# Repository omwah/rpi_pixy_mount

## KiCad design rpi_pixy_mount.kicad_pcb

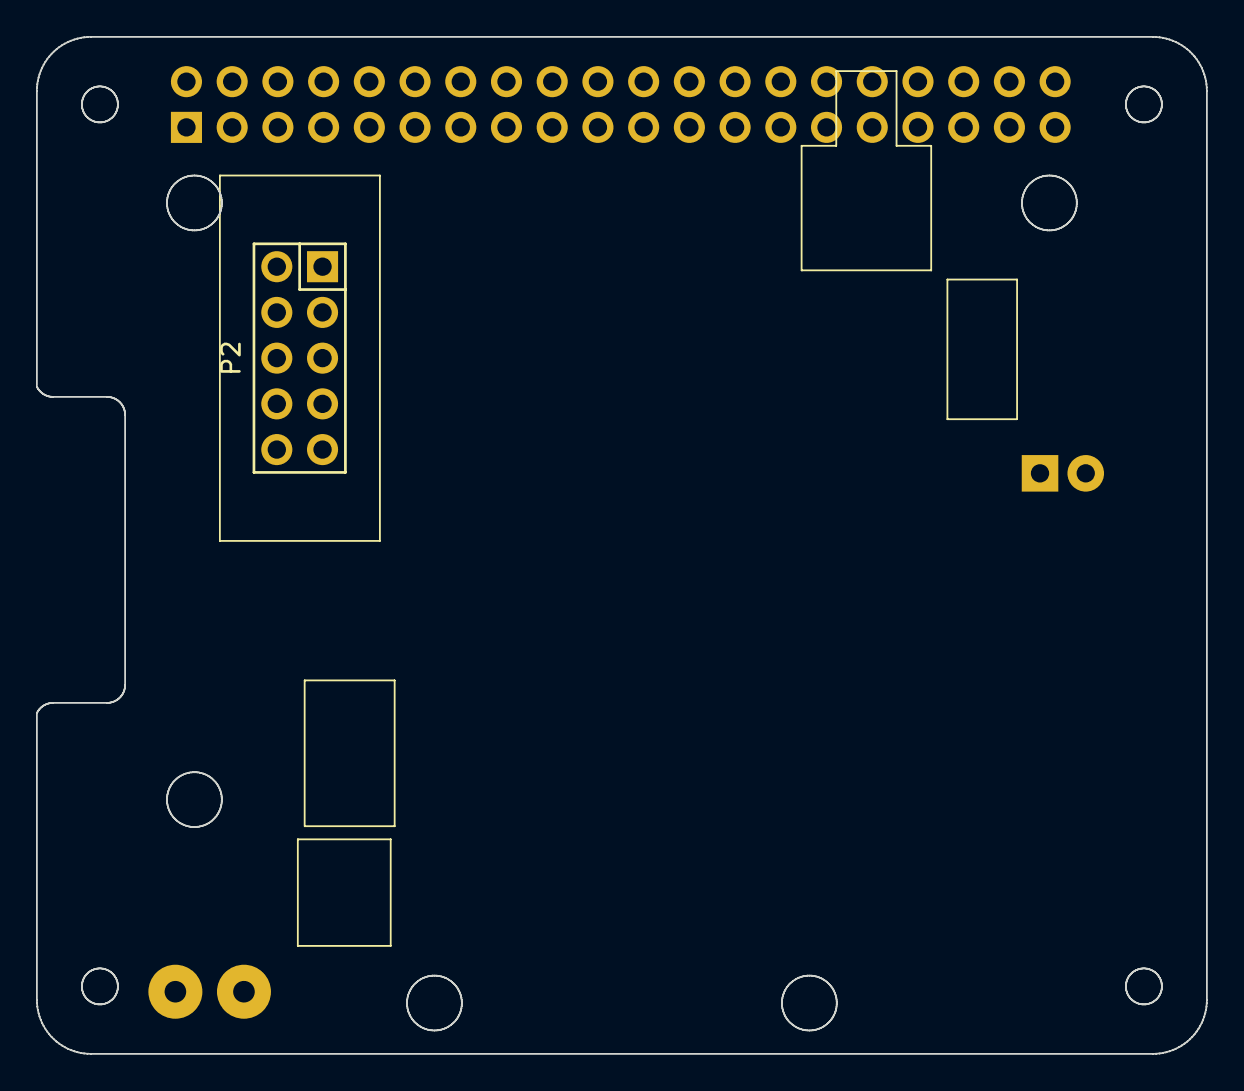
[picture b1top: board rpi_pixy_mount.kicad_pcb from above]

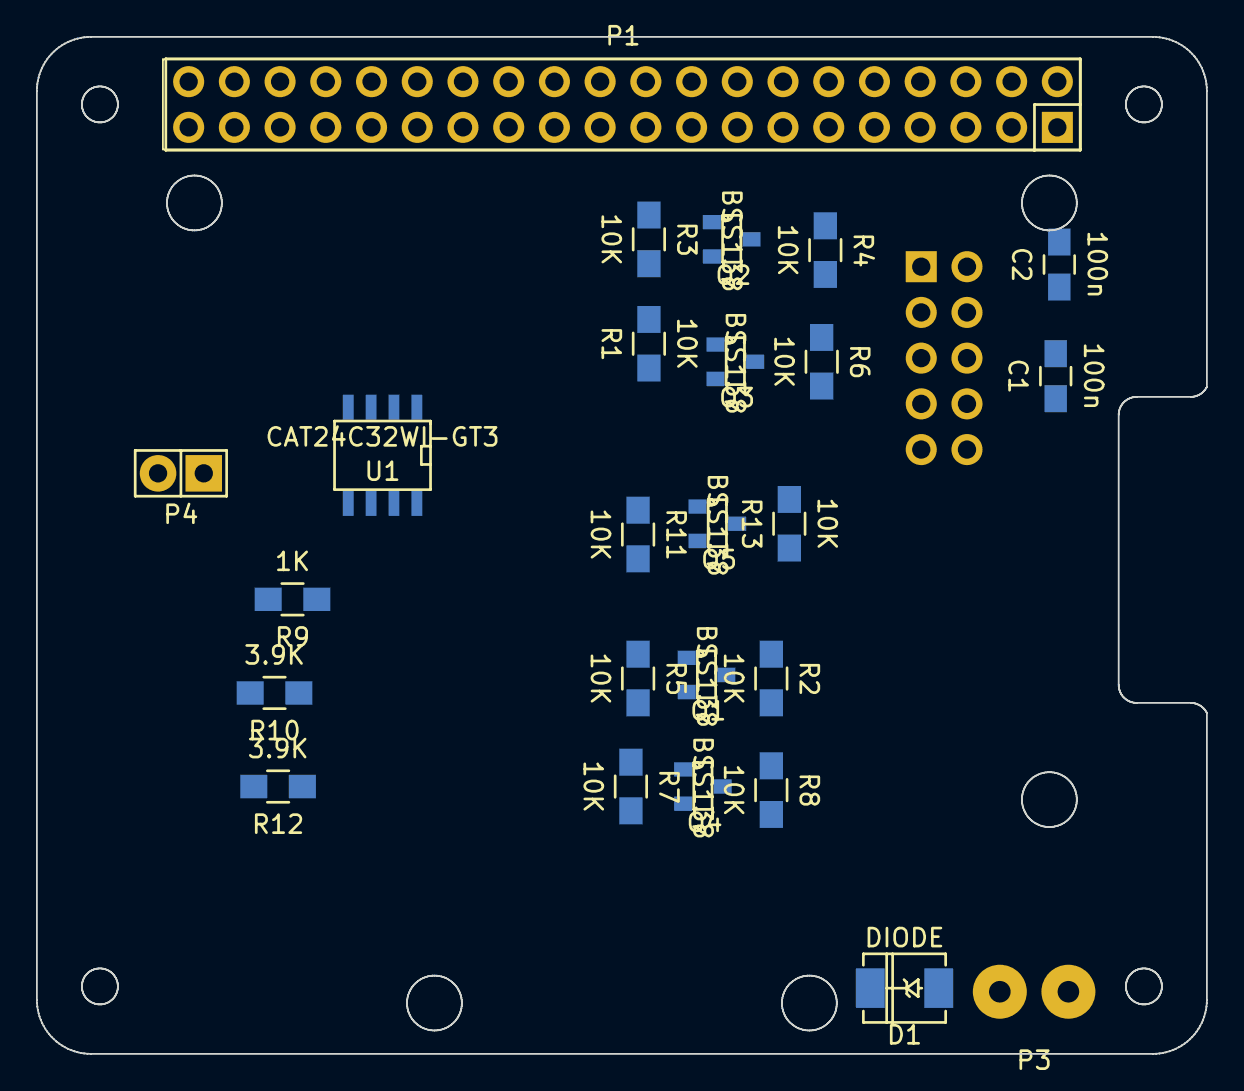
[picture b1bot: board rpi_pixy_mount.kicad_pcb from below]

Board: 2 copper layers, 65.0 x 56.5 mm, 26 parts (25 on the bottom side), 17 nets, no tracks yet.

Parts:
C1, C2: 100n; C_0805_HandSoldering
D1: DIODE; DO-214-AC_SMA
P1: RPi Connector; Socket_Strip_Straight_2x20
P2: Pixy Conn; Socket_Strip_Straight_2x05
P3: Power Input; SolderWirePad_2x_1-2mmDrill
P4: EEProm Write; Pin_Header_Straight_1x02
Q1, Q2, Q3, Q4, Q5: BSS138; SOT-23
R1, R2, R3, R4, R5, R6, R7, R8, R11, R13: 10K; R_0805_HandSoldering
R9: 1K; R_0805_HandSoldering
R10, R12: 3.9K; R_0805_HandSoldering
U1: CAT24C32WI-GT3; SOIC-8-W

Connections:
+3V3: C1.1, P1.1, Q1.1, Q2.1, Q3.1, Q4.1, Q5.1, R1.1, R3.1, R5.1, R7.1, R9.1, R10.1, R11.1, R12.1, U1.8
+5V: C2.1, D1.2, P1.2, P1.4, P2.2, R2.1, R4.1, R6.1, R8.1, R13.1
/ID_SC: P1.28, R10.2, U1.6
/ID_SD: P1.27, R12.2, U1.5
/MISO1: P1.21, Q2.2, R3.2
/MISO2: P2.1, Q2.3, R4.2
/MOSI1: P1.19, Q1.2, R1.2
/MOSI2: P2.4, Q1.3, R2.2
/SCK1: P1.23, Q3.2, R5.2
/SCK2: P2.3, Q3.3, R6.2
/SCL1: P1.5, Q5.2, R11.2
/SCL2: P2.5, Q5.3, R13.2
/SDA1: P1.3, Q4.2, R7.2
/SDA2: P2.9, Q4.3, R8.2
GND: C1.2, C2.2, P1.6, P1.9, P1.14, P1.20, P1.25, P1.30, P1.34, P1.39, P2.6, P2.7, P2.8, P2.10, P4.2, U1.1, U1.2, U1.3, U1.4
unnamed: D1.1, P3.1
unnamed: P4.1, R9.2, U1.7

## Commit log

2015-01-11 Add initial set of files
2015-01-24 Move mounting holes
